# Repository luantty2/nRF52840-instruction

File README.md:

# nRF52840双模键盘指南
## 警告
由于此仓库的原有内容（2020年编写）已严重过期，因此它们已被已经迁移到deprecated分支下。

要制作无线蓝牙键盘，请考虑使用[ZMK](https://zmk.dev/)。

若有特殊原因必须基于QMK制作无线键盘，请考虑使用[Blueism](https://github.com/object-blueism)，Blueism是一种通过UART让Blackpill F411（运行QMK固件）和Seeed XIAO nRF52840（运行Blueism固件）通信的方案，因此它兼容更多QMK特性，但需要自行优化功耗。你可以制作[nrfpill](https://github.com/object-blueism/nrfpill)并烧录[Onekey](https://github.com/object-blueism/blueism_firmware/blob/main/docs/Use%20with%20qmk_firmware.md)样例来测试其功能。

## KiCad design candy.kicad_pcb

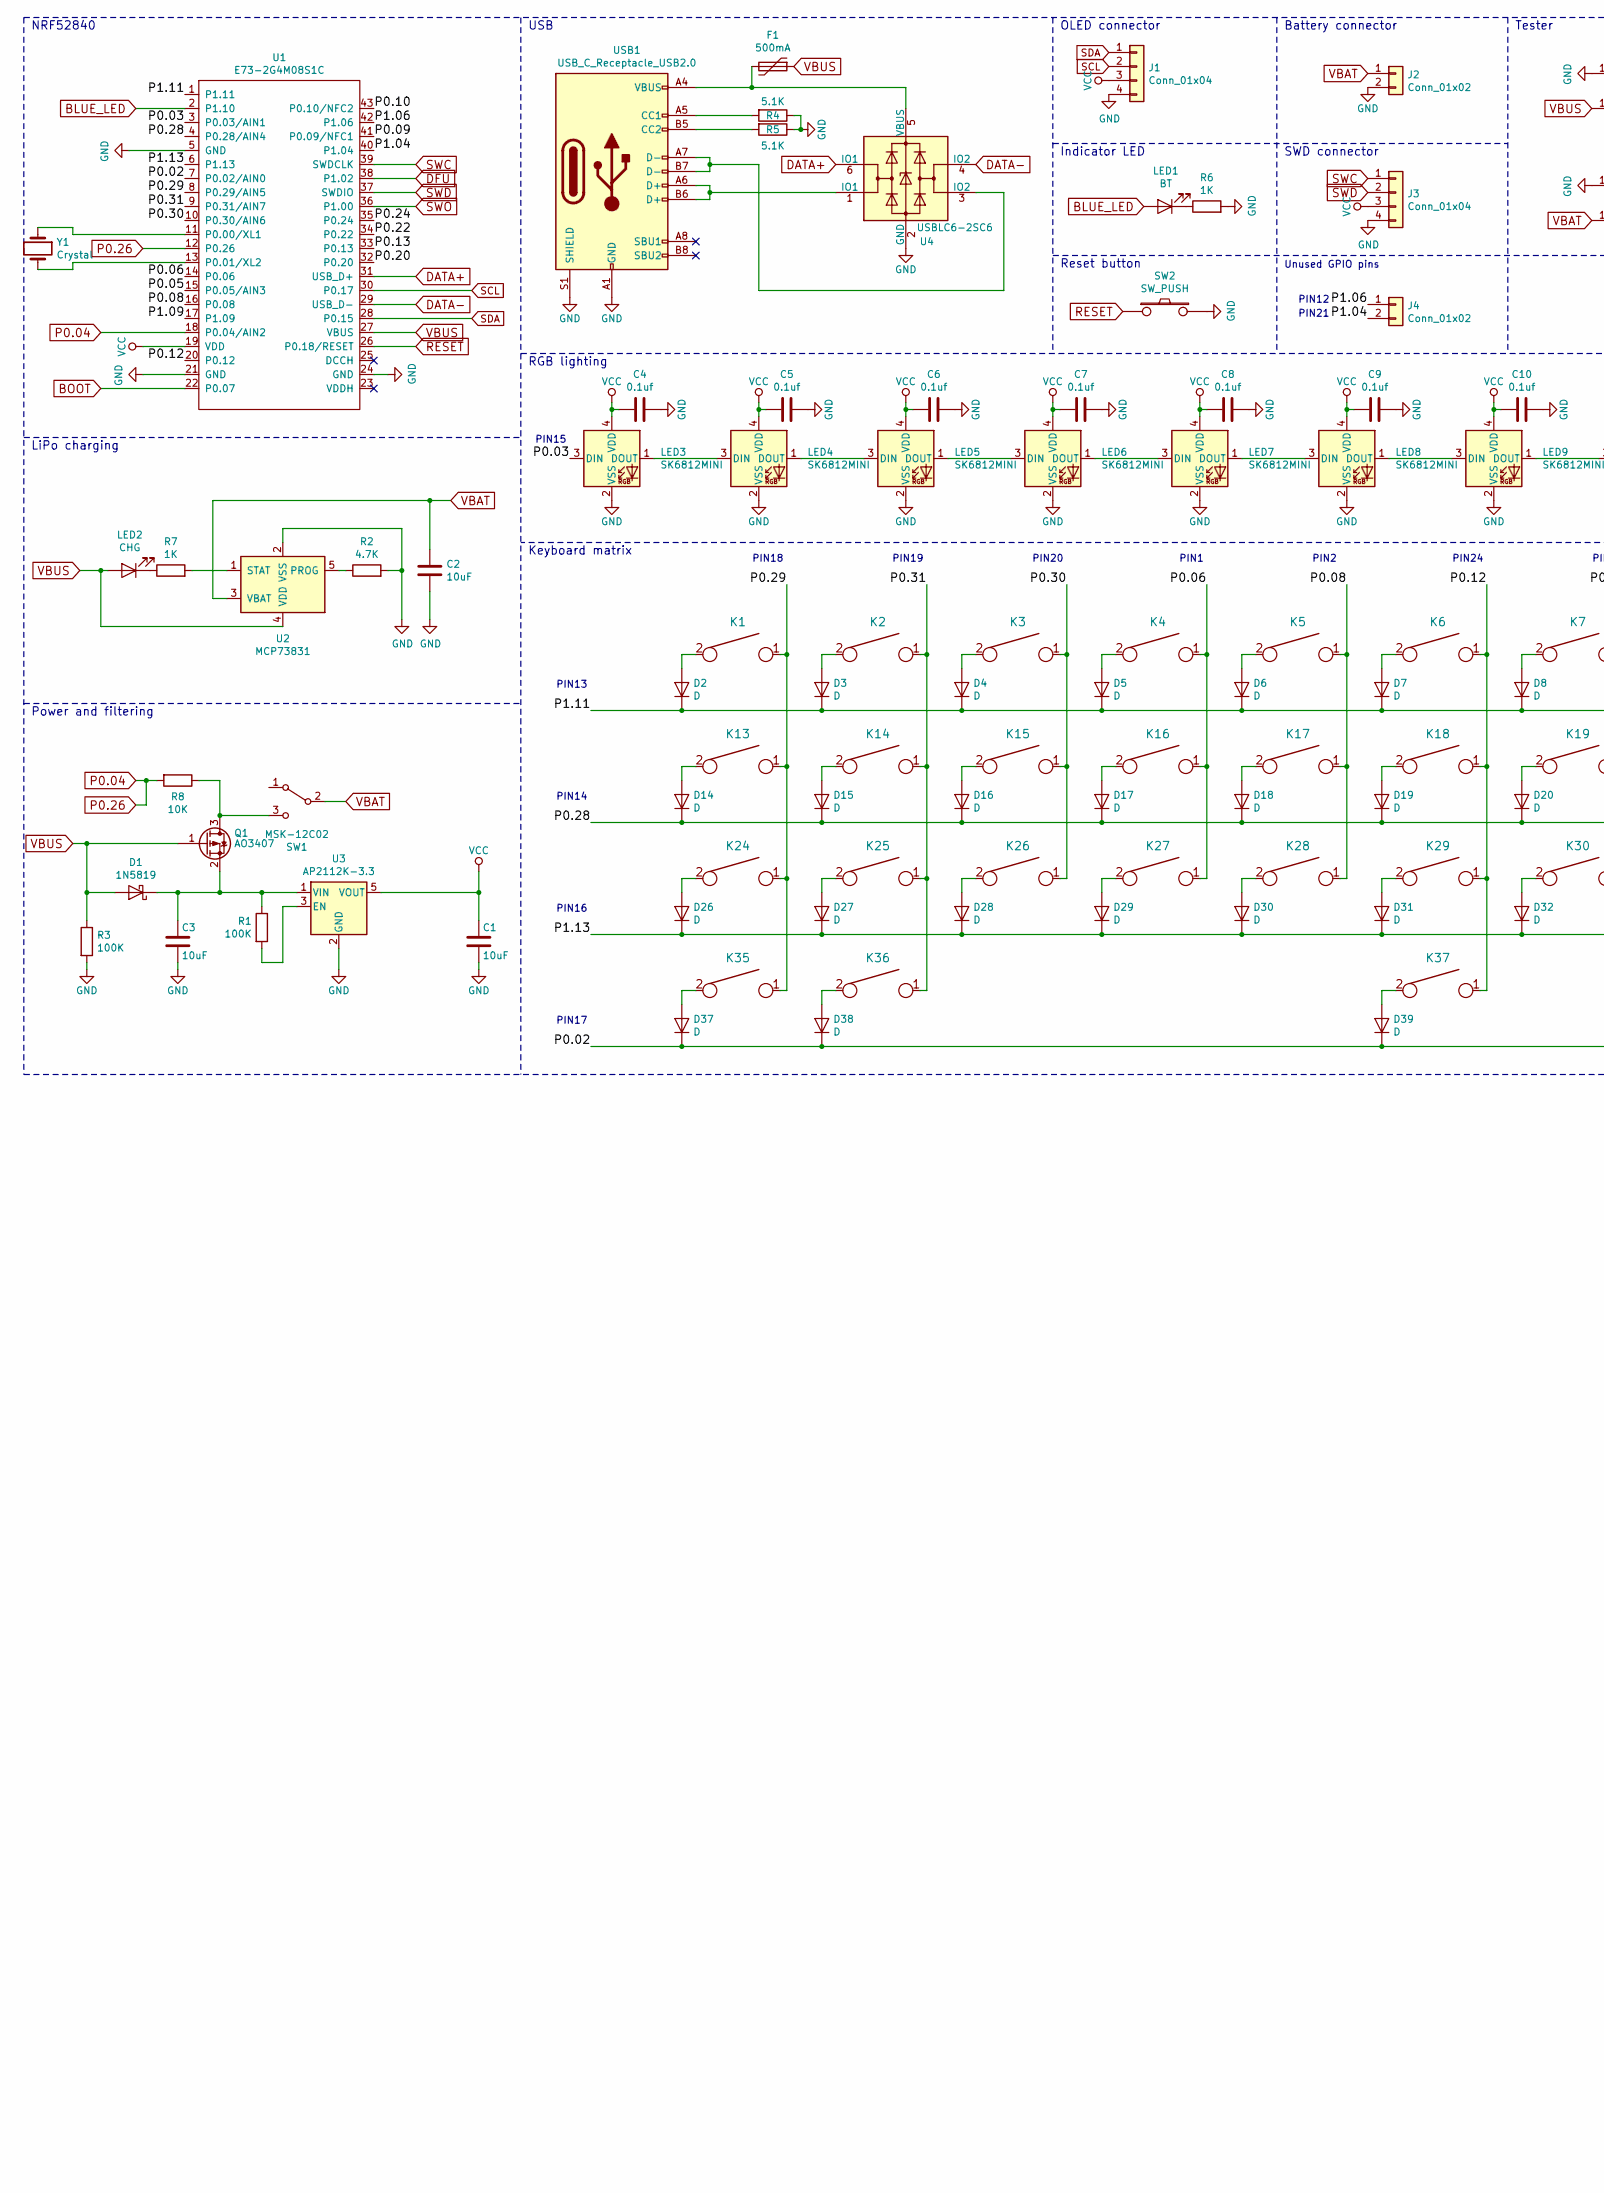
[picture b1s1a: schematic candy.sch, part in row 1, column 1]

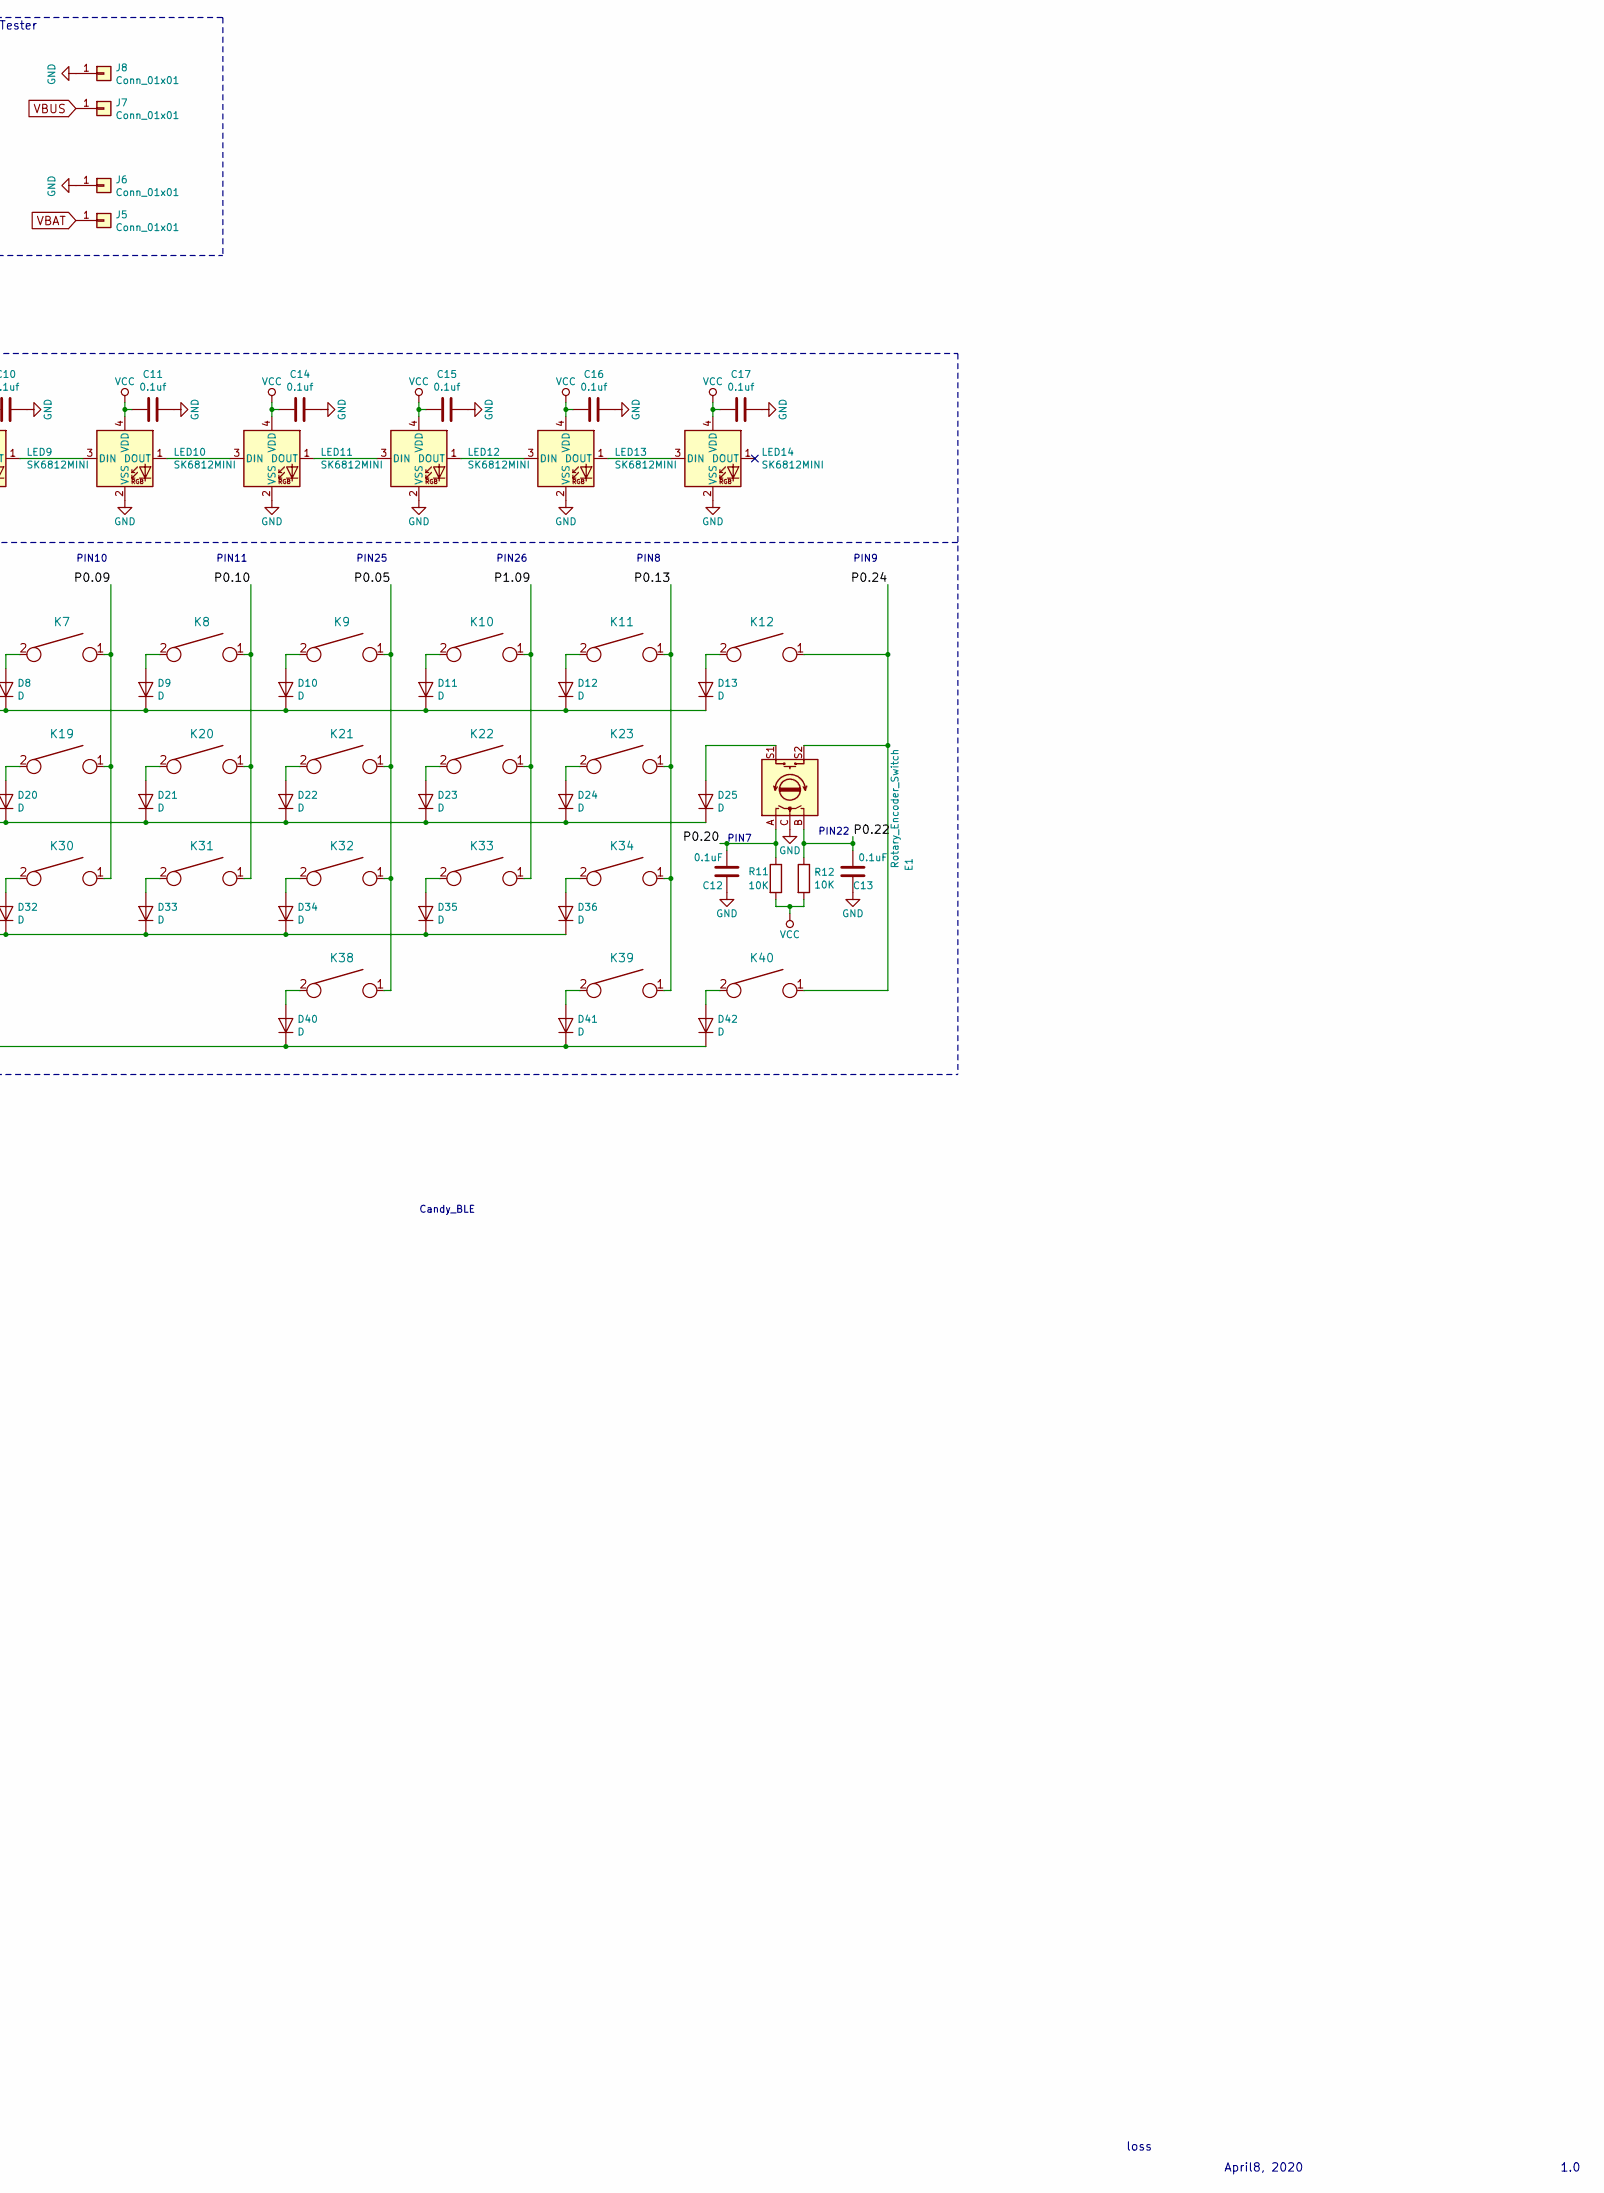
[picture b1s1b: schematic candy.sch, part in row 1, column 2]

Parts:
C1, C2, C3: 10uF; C_0805_2012Metric
C4, C5, C6, C7, C8, C9, C10, C11, C14, C15, C16, C17: 0.1uf; C_0805_2012Metric
C12, C13: 0.1uF; C_0805_2012Metric
D1: 1N5819; D_SOD-123
D2, D3, D4, D5, D6, D7, D8, D9, D10, D11, D12, D13, D14, D15, D16, D17, D18, D19, D20, D21, D22, D23, D24, D25, D26, D27, D28, D29, D30, D31, D32, D33, D34, D35, D36, D37, D38, D39, D40, D41, D42: D; D_SOD-123
E1: Rotary_Encoder_Switch; RotaryEncoder_Alps_EC11E-Switch_Vertical_H20mm
F1: 500mA; Fuse_0805_2012Metric
J1: Conn_01x04; 0.91_SSD1306_OLED
J2: Conn_01x02; PinHeader_1x02_P2.54mm_Horizontal
J3: Conn_01x04; PinHeader_1x04_P2.54mm_Vertical
J4: Conn_01x02; PinHeader_1x02_P2.54mm_Vertical
J5, J6, J7, J8: Conn_01x01; round-square-pads
K1, K2, K3, K4, K5, K6, K7, K8, K9, K10, K11, K12, K14, K15, K16, K17, K18, K19, K20, K21, K22, K25, K26, K27, K28, K29, K30, K31, K32, K33, K34, K38, K39, K40: KEYSW; MXOnly-1U-Hotswap-Round
K13, K35, K36: KEYSW; MXOnly-1.25U-Hotswap-Round
K23, K24: KEYSW; MXOnly-1.75U-Hotswap-Round
K37: KEYSW; MXOnly-6.25U-Hotswap-ReversedStabilizers-Round
LED1: BT; LED_0805_2012Metric
LED2: CHG; LED_0805_2012Metric
LED3, LED4, LED5, LED6, LED7, LED8, LED9, LED10, LED11, LED12, LED13, LED14: SK6812MINI; LED_SK6812MINI_PLCC4_3.5x3.5mm_P1.75mm
Q1: AO3407; SOT-23
R1, R3: 100K; R_0805_2012Metric
R2: 4.7K; R_0805_2012Metric
R4, R5: 5.1K; R_0805_2012Metric
R6, R7: 1K; R_0805_2012Metric
R8, R11, R12: 10K; R_0805_2012Metric
SW1: MSK-12C02; switch_MSK-12C02_smd
SW2: SW_PUSH; SW_DIP_SPSTx01_Slide_6.7x4.1mm_W6.73mm_P2.54mm_LowProfile_J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
U1: E73-2G4M08S1C; E73-2G4M08S1C-52840
U2: MCP73831; SOT-23-5
U3: AP2112K-3.3; SOT-23-5
U4: USBLC6-2SC6; SOT-23-6
USB1: USB_C_Receptacle_USB2.0; USB_C_Receptacle_HRO_TYPE-C-31-M-12
Y1: Crystal; Crystal_SMD_3215-2Pin_3.2x1.5mm

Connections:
/P0.02: D37.1 (K), D38.1 (K), D39.1 (K), D40.1 (K), D41.1 (K), D42.1 (K), U1.7 (P0.02/AIN0)
/P0.03: LED3.3 (DIN), U1.3 (P0.03/AIN1)
/P0.05: K9.1, K21.1, K32.1, K38.1, U1.15 (P0.05/AIN3)
/P0.06: K4.1, K16.1, K27.1, U1.14 (P0.06)
/P0.08: K5.1, K17.1, K28.1, U1.16 (P0.08)
/P0.09: K7.1, K19.1, K30.1, U1.41 (P0.09/NFC1)
/P0.10: K8.1, K20.1, K31.1, U1.43 (P0.10/NFC2)
/P0.12: K6.1, K18.1, K29.1, K37.1, U1.20 (P0.12)
/P0.13: K11.1, K23.1, K34.1, K39.1, U1.33 (P0.13)
/P0.20: C12.2, E1.A, R11.1, U1.32 (P0.20)
/P0.22: C13.2, E1.B, R12.1, U1.34 (P0.22)
/P0.24: E1.S2, K12.1, K40.1, U1.35 (P0.24)
/P0.28: D14.1 (K), D15.1 (K), D16.1 (K), D17.1 (K), D18.1 (K), D19.1 (K), D20.1 (K), D21.1 (K), D22.1 (K), D23.1 (K), D24.1 (K), D25.1 (K), U1.4 (P0.28/AIN4)
/P0.29: K1.1, K13.1, K24.1, K35.1, U1.8 (P0.29/AIN5)
/P0.30: K3.1, K15.1, K26.1, U1.10 (P0.30/AIN6)
/P0.31: K2.1, K14.1, K25.1, K36.1, U1.9 (P0.31/AIN7)
/P1.04: J4.2, U1.40 (P1.04)
/P1.06: J4.1, U1.42 (P1.06)
/P1.09: K10.1, K22.1, K33.1, U1.17 (P1.09)
/P1.11: D2.1 (K), D3.1 (K), D4.1 (K), D5.1 (K), D6.1 (K), D7.1 (K), D8.1 (K), D9.1 (K), D10.1 (K), D11.1 (K), D12.1 (K), D13.1 (K), U1.1 (P1.11)
/P1.13: D26.1 (K), D27.1 (K), D28.1 (K), D29.1 (K), D30.1 (K), D31.1 (K), D32.1 (K), D33.1 (K), D34.1 (K), D35.1 (K), D36.1 (K), U1.6 (P1.13)
BLUE_LED: LED1.2 (A), U1.2 (P1.10)
BOOT: U1.22 (P0.07)
DATA+: U1.31 (USB_D+), U4.6 (IO1)
DATA-: U1.29 (USB_D-), U4.4 (IO2)
DFU: U1.38 (P1.02)
GND: C1.2, C2.2, C3.2, C4.1, C5.1, C6.1, C7.1, C8.1, C9.1, C10.1, C11.1, C12.1, C13.1, C14.1, C15.1, C16.1, C17.1, E1.C, J1.4, J2.2, J3.4, J6.1, J8.1, LED3.2 (VSS), LED4.2 (VSS), LED5.2 (VSS), LED6.2 (VSS), LED7.2 (VSS), LED8.2 (VSS), LED9.2 (VSS), LED10.2 (VSS), LED11.2 (VSS), LED12.2 (VSS), LED13.2 (VSS), LED14.2 (VSS), R2.2, R3.2, R4.1, R5.1, R6.2, SW2.2, U1.5 (GND), U1.21 (GND), U1.24 (GND), U2.2 (VSS), U3.2 (GND), U4.2 (GND), USB1.A1 (GND), USB1.A12 (GND), USB1.B1 (GND), USB1.B12 (GND), USB1.S1 (SHIELD)
unnamed: C3.1, D1.1 (K), Q1.2 (S), R1.1, U3.1 (VIN)
unnamed: D2.2 (A), K1.2
unnamed: D3.2 (A), K2.2
unnamed: D4.2 (A), K3.2
unnamed: D5.2 (A), K4.2
unnamed: D6.2 (A), K5.2
unnamed: D7.2 (A), K6.2
unnamed: D8.2 (A), K7.2
unnamed: D9.2 (A), K8.2
unnamed: D10.2 (A), K9.2
unnamed: D11.2 (A), K10.2
unnamed: D12.2 (A), K11.2
unnamed: D13.2 (A), K12.2
unnamed: D14.2 (A), K13.2
unnamed: D15.2 (A), K14.2
unnamed: D16.2 (A), K15.2
unnamed: D17.2 (A), K16.2
unnamed: D18.2 (A), K17.2
unnamed: D19.2 (A), K18.2
unnamed: D20.2 (A), K19.2
unnamed: D21.2 (A), K20.2
unnamed: D22.2 (A), K21.2
unnamed: D23.2 (A), K22.2
unnamed: D24.2 (A), K23.2
unnamed: D25.2 (A), E1.S1
unnamed: D26.2 (A), K24.2
unnamed: D27.2 (A), K25.2
unnamed: D28.2 (A), K26.2
unnamed: D29.2 (A), K27.2
unnamed: D30.2 (A), K28.2
unnamed: D31.2 (A), K29.2
unnamed: D32.2 (A), K30.2
unnamed: D33.2 (A), K31.2
unnamed: D34.2 (A), K32.2
unnamed: D35.2 (A), K33.2
unnamed: D36.2 (A), K34.2
unnamed: D37.2 (A), K35.2
unnamed: D38.2 (A), K36.2
unnamed: D39.2 (A), K37.2
unnamed: D40.2 (A), K38.2
unnamed: D41.2 (A), K39.2
unnamed: D42.2 (A), K40.2
unnamed: F1.2, U4.5 (VBUS), USB1.A4 (VBUS), USB1.A9 (VBUS), USB1.B4 (VBUS), USB1.B9 (VBUS)
unnamed: LED1.1 (K), R6.1
unnamed: LED2.1 (K), R7.1
unnamed: LED3.1 (DOUT), LED4.3 (DIN)
unnamed: LED4.1 (DOUT), LED5.3 (DIN)
unnamed: LED5.1 (DOUT), LED6.3 (DIN)
unnamed: LED6.1 (DOUT), LED7.3 (DIN)
unnamed: LED7.1 (DOUT), LED8.3 (DIN)
unnamed: LED8.1 (DOUT), LED9.3 (DIN)
unnamed: LED10.1 (DOUT), LED11.3 (DIN)
unnamed: LED9.1 (DOUT), LED10.3 (DIN)
unnamed: LED11.1 (DOUT), LED12.3 (DIN)
unnamed: LED12.1 (DOUT), LED13.3 (DIN)
unnamed: LED13.1 (DOUT), LED14.3 (DIN)
unnamed: Q1.3 (D), R8.1, SW1.3 (C)
unnamed: R1.2, U3.3 (EN)
unnamed: R2.1, U2.5 (PROG)
unnamed: R4.2, USB1.A5 (CC1)
unnamed: R5.2, USB1.B5 (CC2)
unnamed: R7.2, U2.1 (STAT)
unnamed: U1.11 (P0.00/XL1), Y1.1
unnamed: U1.13 (P0.01/XL2), Y1.2
unnamed: U4.1 (IO1), USB1.A6 (D+), USB1.B6 (D+)
unnamed: U4.3 (IO2), USB1.A7 (D-), USB1.B7 (D-)
P0.04: R8.2, U1.12 (P0.26), U1.18 (P0.04/AIN2)
RESET: SW2.1, U1.26 (P0.18/RESET)
SCL: J1.2, U1.30 (P0.17)
SDA: J1.1, U1.28 (P0.15)
SWC: J3.1, U1.39 (SWDCLK)
SWD: J3.2, U1.37 (SWDIO)
SWO: U1.36 (P1.00)
VBAT: C2.1, J2.1, J5.1, SW1.2 (B), U2.3 (VBAT)
VBUS: D1.2 (A), F1.1, J7.1, LED2.2 (A), Q1.1 (G), R3.1, U1.27 (VBUS), U2.4 (VDD)
VCC: C1.1, C4.2, C5.2, C6.2, C7.2, C8.2, C9.2, C10.2, C11.2, C14.2, C15.2, C16.2, C17.2, J1.3, J3.3, LED3.4 (VDD), LED4.4 (VDD), LED5.4 (VDD), LED6.4 (VDD), LED7.4 (VDD), LED8.4 (VDD), LED9.4 (VDD), LED10.4 (VDD), LED11.4 (VDD), LED12.4 (VDD), LED13.4 (VDD), LED14.4 (VDD), R11.2, R12.2, U1.19 (VDD), U3.5 (VOUT)

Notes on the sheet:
Power and filtering
LiPo charging
loss
April8, 2020
1.0
PIN13
PIN14
PIN16
PIN17
PIN18
PIN19
PIN20
PIN1
PIN2
PIN24
PIN10
PIN11
PIN25
PIN26
PIN8
PIN9
PIN7
PIN22
PIN12
PIN21
Unused GPIO pins
PIN15
NRF52840
USB
OLED connector
Indicator LED
Reset button
Battery connector
SWD connector
Tester
RGB lighting
Keyboard matrix
Candy_BLE

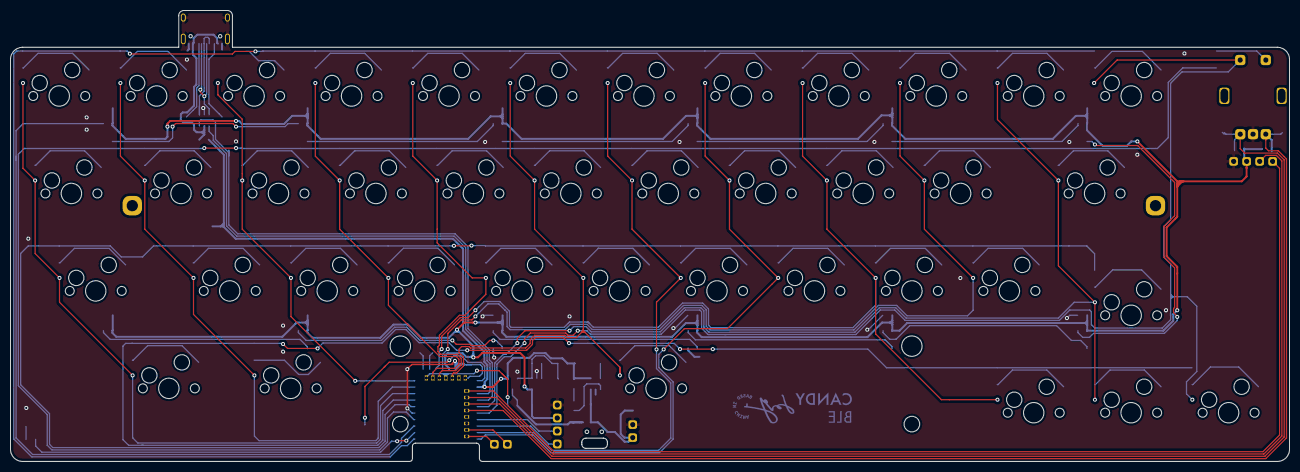
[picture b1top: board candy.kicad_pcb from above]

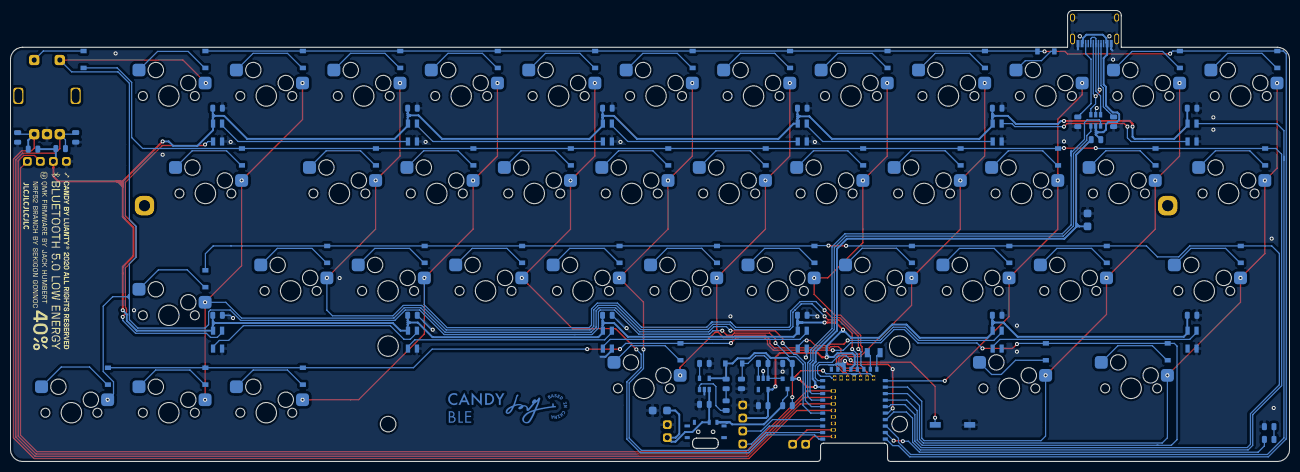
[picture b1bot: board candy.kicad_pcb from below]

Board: 2 copper layers, 250.0 x 88.2 mm, 142 parts (100 on the bottom side), 100 nets.

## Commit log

2020-04-30 init
2020-04-30 esc_update
2020-05-02 a lot of firmware changes
2020-05-02 cleanup encoder code
2020-05-03 modify 'tap_code()'
    modify 'tap_code()' to 'register_code()' and 'unregister_code()'
2020-05-07 Fix USB RGB
2020-05-10 firmware update
